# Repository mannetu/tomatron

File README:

// Software SPI (slower updates, more flexible pin options):
// pin 7 - Serial clock out (SCLK)
// pin 6 - Serial data out (DIN)
// pin 5 - Data/Command select (D/C)
// pin 4 - LCD chip select (CS)
// pin 3 - LCD reset (RST)
//Adafruit_PCD8544 display = Adafruit_PCD8544(7, 6, 5, 4, 3);

// Hardware SPI (faster, but must use certain hardware pins):
// SCK is LCD serial clock (SCLK) - this is pin 13 on Arduino Uno
// MOSI is LCD DIN - this is pin 11 on an Arduino Uno
// pin 5 - Data/Command select (D/C)
// pin 4 - LCD chip select (CS)
// pin 3 - LCD reset (RST)
Adafruit_PCD8544 display = Adafruit_PCD8544(8, 7, 6);
// Note with hardware SPI MISO and SS pins aren't used but will still be read
// and written to during SPI transfer.  Be careful sharing these pins!

#define NUMFLAKES 10
#define XPOS 0
#define YPOS 1
#define DELTAY 2

#define LOGO16_GLCD_HEIGHT 16
#define LOGO16_GLCD_WIDTH  16

static const unsigned char PROGMEM logo16_glcd_bmp[] =
{ B00000000, B00000000,
 B00000000, B00000000,
 B00000000, B00000000,
 B00000000, B00000000,
 B00000000, B00000000,
 B00000000, B00000000,
 B00000000, B00000000,
 B00000000, B00000000,
 B00000000, B00000000,
 B00000000, B00000000,
 B00000000, B00000000,
 B00000000, B00000000,
 B00000000, B00000000,
 B00000000, B00000000,
 B00000000, B00000000,
 B00000000, B00000000 };

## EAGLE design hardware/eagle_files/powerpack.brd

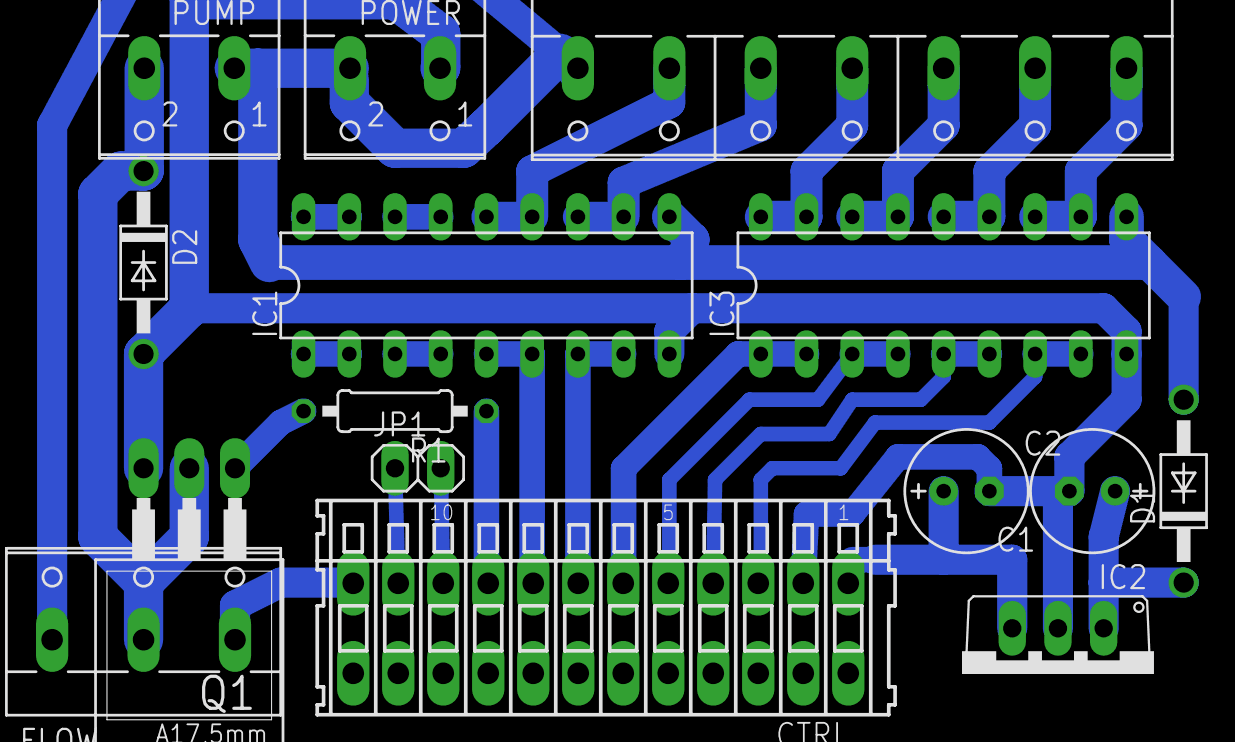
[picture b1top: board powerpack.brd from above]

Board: 2 copper layers, 15 parts (0 on the bottom side), 26 nets.

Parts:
C1, C2: E2,5-7
CTRL: 233-112
D1, D2: 1N4004; DO41-10
FLOW: W237-133
IC1, IC3: DIL18
IC2: 7805TV; TO220V
JP1: 1X02
POWER: W237-102
PUMP: W237-102
Q1: IRLZ44Z; TO220BH
R1: 1,2k; 0207/10
VALVES: W237-7P

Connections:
+5V: C2.+, CTRL.B1, IC2.3
+12V: D1.A, FLOW.1, IC1.10, IC3.10, POWER.2, PUMP.1, VALVES.7
GND: C1.-, C2.-, CTRL.B2, D2.A, IC1.9, IC2.2, IC3.9, POWER.1, Q1.S
unnamed: C1.+, D1.C, IC2.1
unnamed: CTRL.B12, FLOW.3
unnamed: CTRL.B11, JP1.1
unnamed: CTRL.B10, JP1.2
unnamed: IC1.1, IC1.2
unnamed: IC1.3, IC1.4
unnamed: CTRL.B8, IC1.5, IC1.6
unnamed: CTRL.B7, IC1.7, IC1.8
unnamed: IC1.17, IC1.18
unnamed: IC1.15, IC1.16
unnamed: IC1.13, IC1.14, VALVES.6
unnamed: IC1.11, IC1.12, VALVES.5
unnamed: Q1.G, R1.2
unnamed: D2.C, FLOW.2, PUMP.2, Q1.D
unnamed: IC3.17, IC3.18, VALVES.4
unnamed: IC3.15, IC3.16, VALVES.3
unnamed: IC3.13, IC3.14, VALVES.2
unnamed: IC3.11, IC3.12, VALVES.1
unnamed: CTRL.B3, IC3.7, IC3.8
unnamed: CTRL.B4, IC3.5, IC3.6
unnamed: CTRL.B5, IC3.3, IC3.4
unnamed: CTRL.B6, IC3.1, IC3.2
unnamed: CTRL.B9, R1.1

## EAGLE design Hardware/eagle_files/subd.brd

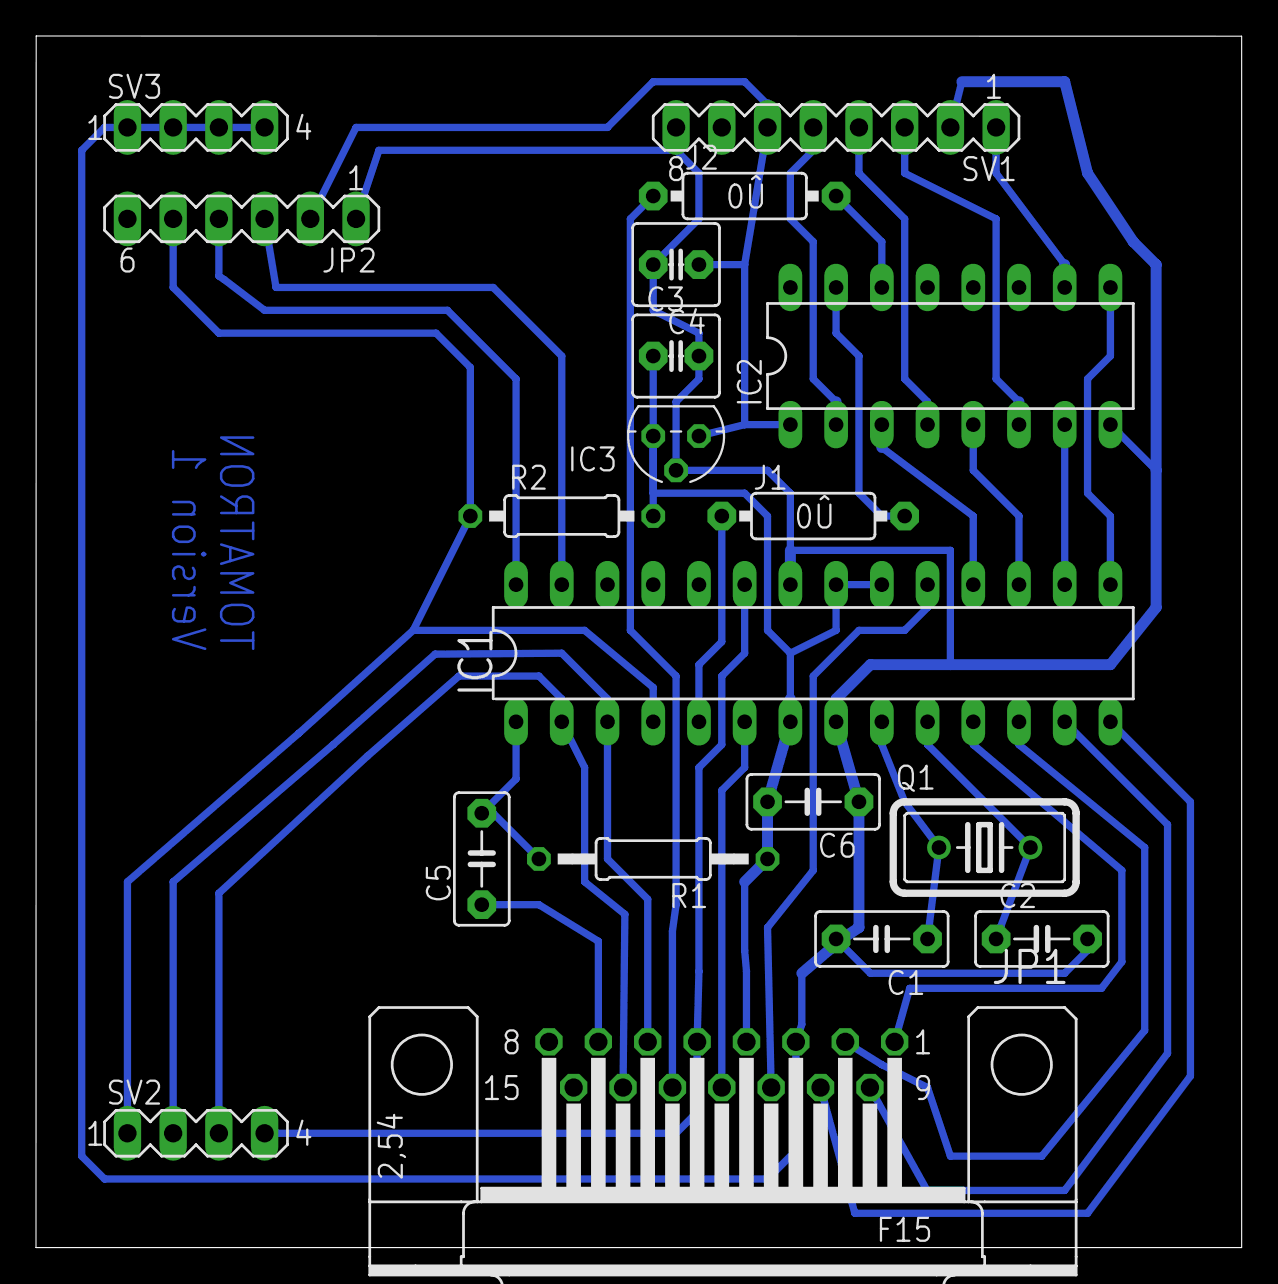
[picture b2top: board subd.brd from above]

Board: 2 copper layers, 67.0 x 67.3 mm, 19 parts (0 on the bottom side), 31 nets.

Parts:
C1, C2, C5, C6: C5B3
C3, C4: C2.5-5
IC1: ATMEGA328-20P; DIL28-3
IC2: 4050N; DIL16
IC3: LP2950ACZ-3.3; TO92
J1, J2: 0R/10
JP1: F15H
JP2: MA06-1
Q1: HC18U-V
R1: 10k; 0207/12
R2: 0207/10
SV1: MA08-1
SV2, SV3: MA04-1

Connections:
+5V: C3.1, C6.2, IC1.7, IC1.20, IC1.21, IC3.3, JP1.4, R1.1, R2.2
unnamed: C1.1, IC1.9, Q1.1
unnamed: C2.1, IC1.10, Q1.2
unnamed: IC1.14, JP1.10
unnamed: IC1.13, JP1.9
unnamed: IC1.15, IC2.9
unnamed: IC1.16, IC2.7
unnamed: IC1.17, IC2.5
unnamed: IC1.18, IC2.3
unnamed: IC2.2, SV1.5
unnamed: IC2.4, SV1.4
unnamed: IC2.6, SV1.3
unnamed: IC2.10, SV1.1
unnamed: IC1.12, JP1.2
unnamed: IC1.11, JP1.1
unnamed: IC1.6, JP1.12
unnamed: IC1.5, J1.1
unnamed: C5.1, JP1.7
unnamed: C5.2, IC1.1, R1.2
unnamed: IC1.27, JP2.3
unnamed: IC1.28, JP2.4
unnamed: IC1.4, JP2.5, R2.1, SV2.1
unnamed: IC1.3, JP1.6, SV2.2
unnamed: IC1.2, JP1.14, SV2.3
unnamed: IC2.14, J2.2
unnamed: IC1.23, JP1.5, SV2.4
unnamed: IC2.15, J1.2
unnamed: J2.1, JP1.13
unnamed: IC1.19, JP1.11
VDD: C4.1, IC2.1, IC3.1, JP2.2, SV1.6
VSS: C1.2, C2.2, C3.2, C4.2, C6.1, IC1.8, IC1.22, IC2.8, IC3.2, JP1.3, JP2.1, SV1.2, SV1.8, SV3.1, SV3.2, SV3.3, SV3.4

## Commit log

2016-05-09 blubb
2016-05-15 Added classes for valves and flowmeter
2016-05-16 test abgeschlossen
2016-05-16 water.h and water.cpp
2016-05-16 Volumen-Einstellung hinzugefügt
2016-05-23 code cleaned-up
2016-05-24 call Giessen every 500ms
2016-05-26 target set and read fixed
2016-05-26 fixed interrupt
2016-05-26 calibration routine not fully fixed
2016-05-26 calibration fixed
2016-05-27 fixed display stuff
2016-05-28 added clock and timer set to volume set routine
2016-05-28 added giessTime as time_t and write/read to/from EEPROM
2016-05-29 funktioniert
2016-05-29 menu führung verbessert
2016-05-29 long für lastActivity
2016-05-29 added pump and switched display to software SPI
2016-05-29 added pump start/stop to calibration
2016-05-29 changed pins and set free 2 GPIOs
2016-05-30 added plantname to display
2016-05-31 added constructors
2016-05-31 put giess variables in struct
2016-06-12 changed pins
2016-06-13 SPI lib removed
2016-06-14 Sleep interrupted by WDT and external interrupt
2016-06-16 corrected BSY enumeration
2016-06-16 corrected BSY enumeration2
2016-06-17 sleepmode and wdt improved
2016-06-20 RTC implemented
2016-07-02 test flow meter works
2016-07-02 Initialize Giessflag
2016-07-06 RTC interups works
2016-07-13 funzt
2016-07-13 fertig
2016-08-03 blubb2
2016-09-16 Hardware folder added
2016-10-02 added Temp correction
2016-10-02 changed to 6 channels and rearranged display
2016-10-03 added powerpack.sch
2016-10-03 added thermoCoeff to setParameters
2016-10-05 bugs fixed
2016-10-10 Powerpack Eagle File
2016-10-27 Version 1.0
2017-03-19 added manualMode
2017-03-21 blubb+
2017-03-21 super
2017-03-24 version 2.0
2017-04-03 blink water
2017-04-06 Timer on/off
2017-04-06 manual start program
2017-04-17 aufgeraeumt
